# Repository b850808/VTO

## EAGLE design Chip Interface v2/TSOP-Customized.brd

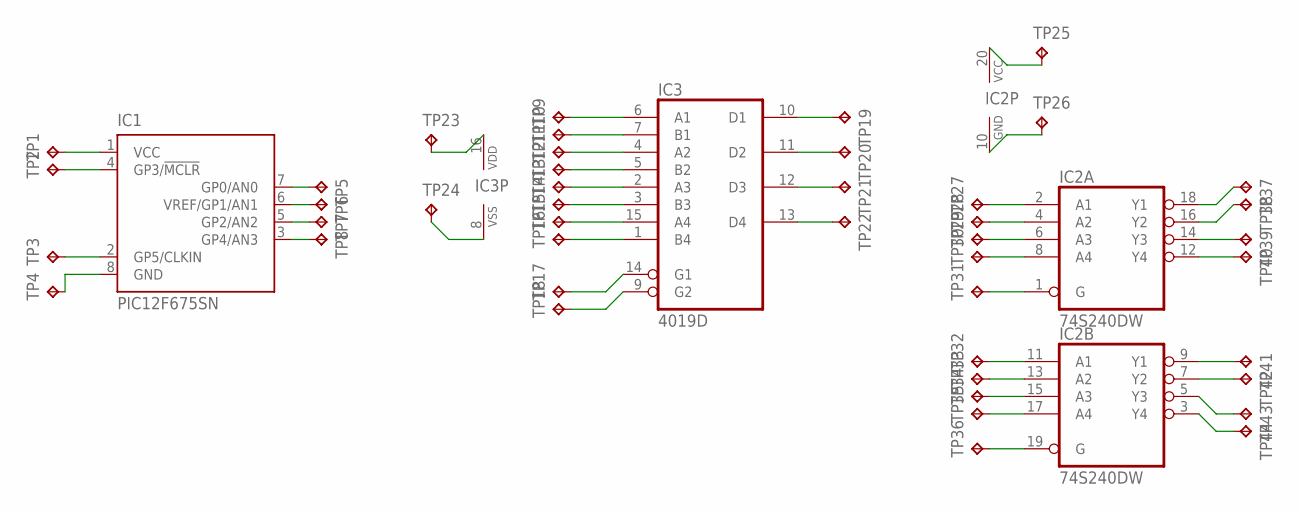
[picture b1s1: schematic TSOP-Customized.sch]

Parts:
IC1: PIC12F675SN; SO-08
IC2: 74S240DW; SO20W
IC3: 4019D; SO16
TP1, TP2, TP3, TP4, TP5, TP6, TP7, TP8, TP9, TP10, TP11, TP12, TP13, TP14, TP15, TP16, TP17, TP18, TP19, TP20, TP21, TP22, TP23, TP24, TP25, TP26, TP27, TP28, TP29, TP30, TP31, TP32, TP33, TP34, TP35, TP36, TP37, TP38, TP39, TP40, TP41, TP42, TP43, TP44: TPPAD1-13Y; P1-13Y

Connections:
unnamed: IC1.1 (VCC), TP1.TP
unnamed: IC1.4 (GP3/!MCLR), TP2.TP
unnamed: IC1.2 (GP5/CLKIN), TP3.TP
unnamed: IC1.8 (GND), TP4.TP
unnamed: IC1.3 (GP4/AN3), TP8.TP
unnamed: IC1.5 (GP2/AN2), TP7.TP
unnamed: IC1.6 (VREF/GP1/AN1), TP6.TP
unnamed: IC1.7 (GP0/AN0), TP5.TP
unnamed: IC3.6 (A1), TP9.TP
unnamed: IC3.7 (B1), TP10.TP
unnamed: IC3.4 (A2), TP11.TP
unnamed: IC3.5 (B2), TP12.TP
unnamed: IC3.2 (A3), TP13.TP
unnamed: IC3.3 (B3), TP14.TP
unnamed: IC3.15 (A4), TP15.TP
unnamed: IC3.1 (B4), TP16.TP
unnamed: IC3.14 (G1), TP17.TP
unnamed: IC3.9 (G2), TP18.TP
unnamed: IC3.13 (D4), TP22.TP
unnamed: IC3.12 (D3), TP21.TP
unnamed: IC3.11 (D2), TP20.TP
unnamed: IC3.10 (D1), TP19.TP
unnamed: IC3.8 (VSS), TP24.TP
unnamed: IC3.16 (VDD), TP23.TP
unnamed: IC2.2 (A1), TP27.TP
unnamed: IC2.4 (A2), TP28.TP
unnamed: IC2.6 (A3), TP29.TP
unnamed: IC2.8 (A4), TP30.TP
unnamed: IC2.1 (G), TP31.TP
unnamed: IC2.11 (A1), TP32.TP
unnamed: IC2.13 (A2), TP33.TP
unnamed: IC2.15 (A3), TP34.TP
unnamed: IC2.17 (A4), TP35.TP
unnamed: IC2.19 (G), TP36.TP
unnamed: IC2.20 (VCC), TP25.TP
unnamed: IC2.10 (GND), TP26.TP
unnamed: IC2.18 (Y1), TP37.TP
unnamed: IC2.16 (Y2), TP38.TP
unnamed: IC2.14 (Y3), TP39.TP
unnamed: IC2.12 (Y4), TP40.TP
unnamed: IC2.9 (Y1), TP41.TP
unnamed: IC2.7 (Y2), TP42.TP
unnamed: IC2.5 (Y3), TP43.TP
unnamed: IC2.3 (Y4), TP44.TP

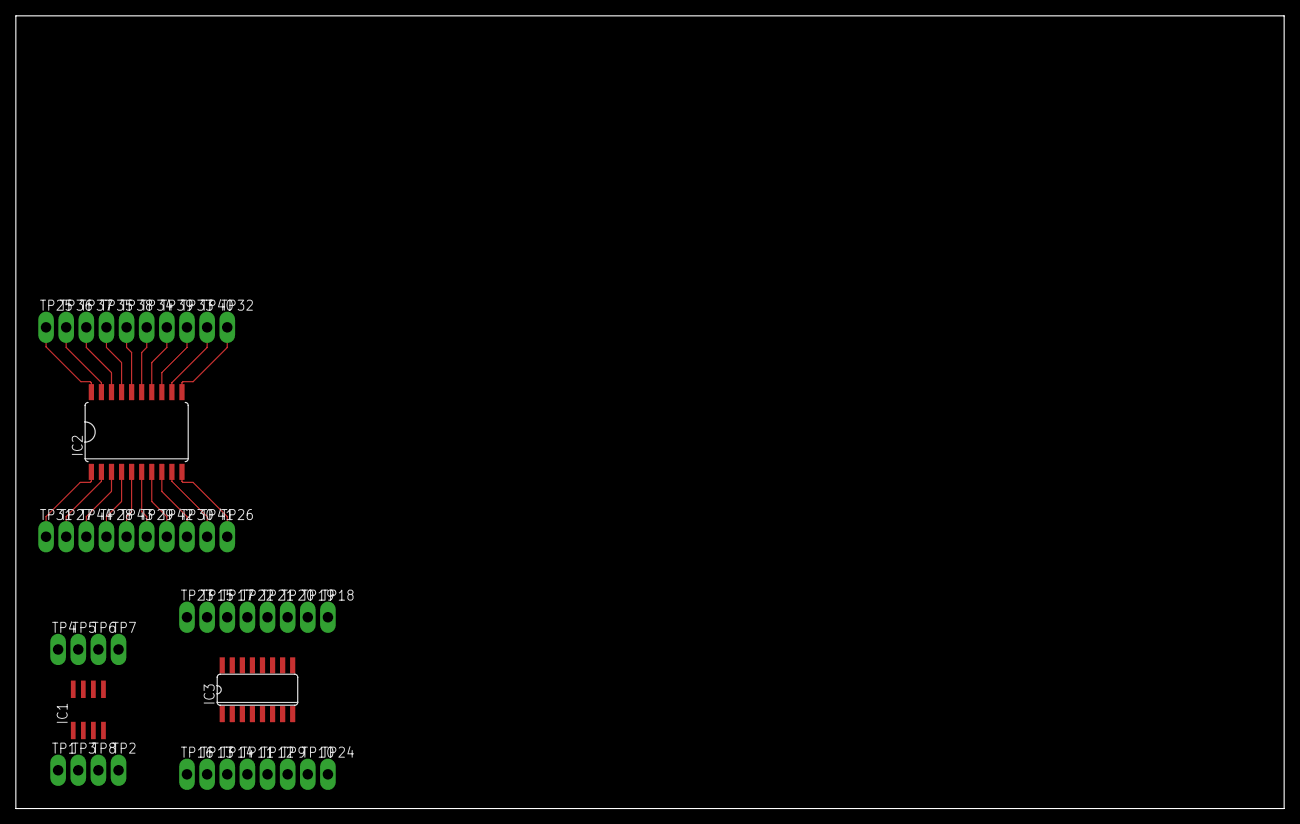
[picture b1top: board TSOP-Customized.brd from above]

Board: 2 copper layers, 160.0 x 100.0 mm, 47 parts (0 on the bottom side), 44 nets.

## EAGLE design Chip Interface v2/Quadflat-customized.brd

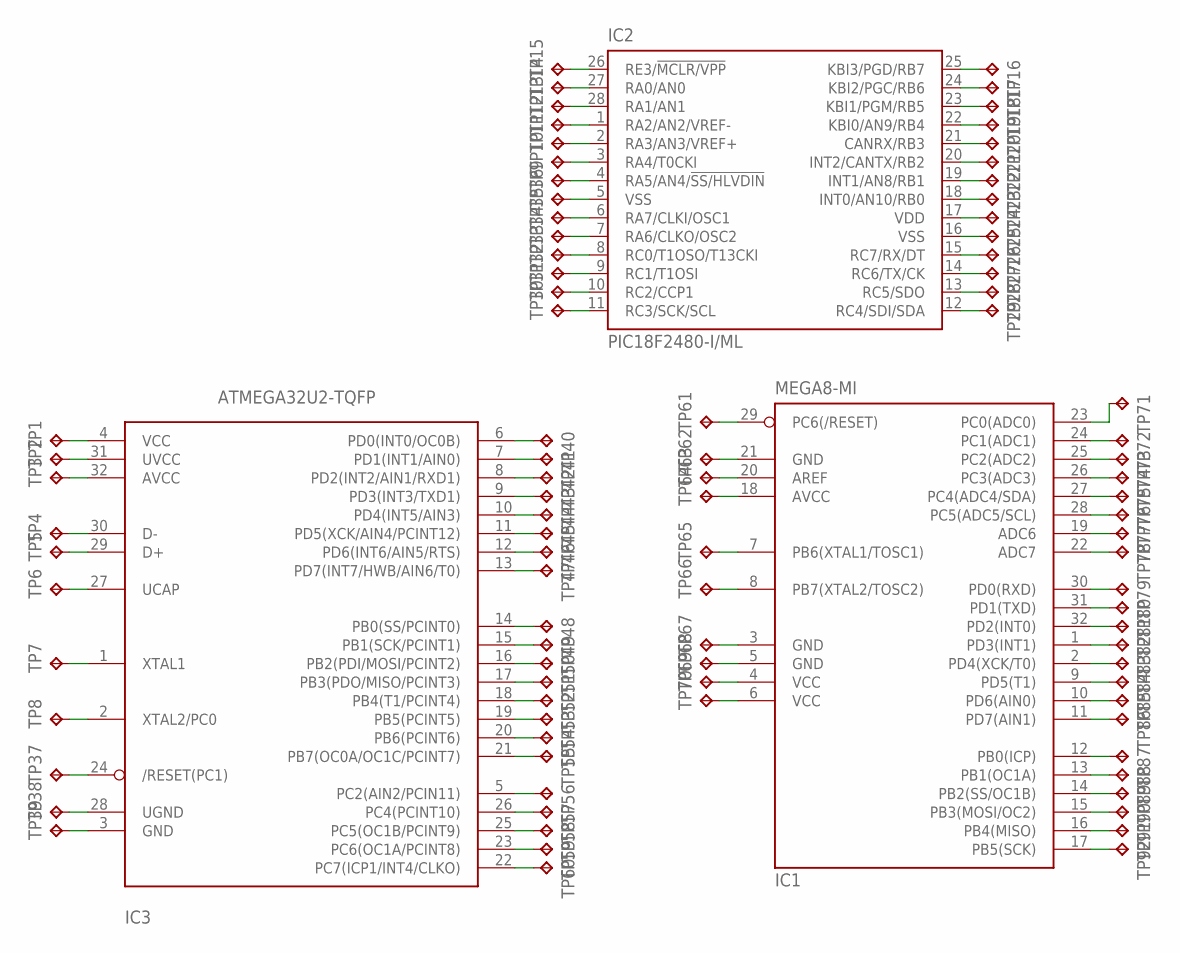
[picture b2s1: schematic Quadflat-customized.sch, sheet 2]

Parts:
IC1: MEGA8-MI; MLF32
IC2: PIC18F2480-I/ML; QFN28-ML_6X6MM
IC3: ATMEGA32U2-TQFP; TQFP32-08
TP1, TP2, TP3, TP4, TP5, TP6, TP7, TP8, TP9, TP10, TP11, TP12, TP13, TP14, TP15, TP16, TP17, TP18, TP19, TP20, TP21, TP22, TP23, TP24, TP25, TP26, TP27, TP28, TP29, TP30, TP31, TP32, TP33, TP34, TP35, TP36, TP37, TP38, TP39, TP40, TP41, TP42, TP43, TP44, TP45, TP46, TP47, TP48, TP49, TP50, TP51, TP52, TP53, TP54, TP55, TP56, TP57, TP58, TP59, TP60, TP61, TP62, TP63, TP64, TP65, TP66, TP67, TP68, TP69, TP70, TP71, TP72, TP73, TP74, TP75, TP76, TP77, TP78, TP79, TP80, TP81, TP82, TP83, TP84, TP85, TP86, TP87, TP88, TP89, TP90, TP91, TP92: TPPAD1-13Y; P1-13Y

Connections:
unnamed: IC3.4 (VCC), TP1.TP
unnamed: IC3.31 (UVCC), TP2.TP
unnamed: IC3.32 (AVCC), TP3.TP
unnamed: IC3.30 (D-), TP4.TP
unnamed: IC3.29 (D+), TP5.TP
unnamed: IC3.27 (UCAP), TP6.TP
unnamed: IC3.1 (XTAL1), TP7.TP
unnamed: IC3.2 (XTAL2/PC0), TP8.TP
unnamed: IC2.11 (RC3/SCK/SCL), TP30.TP
unnamed: IC2.10 (RC2/CCP1), TP31.TP
unnamed: IC2.9 (RC1/T1OSI), TP32.TP
unnamed: IC2.8 (RC0/T1OSO/T13CKI), TP33.TP
unnamed: IC2.7 (RA6/CLKO/OSC2), TP34.TP
unnamed: IC2.6 (RA7/CLKI/OSC1), TP35.TP
unnamed: IC2.5 (VSS), TP36.TP
unnamed: IC2.4 (RA5/AN4/!SS/HLVDIN), TP9.TP
unnamed: IC2.3 (RA4/T0CKI), TP10.TP
unnamed: IC2.2 (RA3/AN3/VREF+), TP11.TP
unnamed: IC2.1 (RA2/AN2/VREF-), TP12.TP
unnamed: IC2.28 (RA1/AN1), TP13.TP
unnamed: IC2.27 (RA0/AN0), TP14.TP
unnamed: IC2.26 (RE3/!MCLR/VPP), TP15.TP
unnamed: IC2.25 (KBI3/PGD/RB7), TP16.TP
unnamed: IC2.24 (KBI2/PGC/RB6), TP17.TP
unnamed: IC2.23 (KBI1/PGM/RB5), TP18.TP
unnamed: IC2.22 (KBI0/AN9/RB4), TP19.TP
unnamed: IC2.21 (CANRX/RB3), TP20.TP
unnamed: IC2.20 (INT2/CANTX/RB2), TP21.TP
unnamed: IC2.19 (INT1/AN8/RB1), TP22.TP
unnamed: IC2.18 (INT0/AN10/RB0), TP23.TP
unnamed: IC2.17 (VDD), TP24.TP
unnamed: IC2.16 (VSS), TP25.TP
unnamed: IC2.15 (RC7/RX/DT), TP26.TP
unnamed: IC2.14 (RC6/TX/CK), TP27.TP
unnamed: IC2.13 (RC5/SDO), TP28.TP
unnamed: IC2.12 (RC4/SDI/SDA), TP29.TP
unnamed: IC3.24 (/RESET(PC1)), TP37.TP
unnamed: IC3.28 (UGND), TP38.TP
unnamed: IC3.3 (GND), TP39.TP
unnamed: IC3.22 (PC7(ICP1/INT4/CLKO)), TP60.TP
unnamed: IC3.23 (PC6(OC1A/PCINT8)), TP59.TP
unnamed: IC3.25 (PC5(OC1B/PCINT9)), TP58.TP
unnamed: IC3.26 (PC4(PCINT10)), TP57.TP
unnamed: IC3.5 (PC2(AIN2/PCIN11)), TP56.TP
unnamed: IC3.21 (PB7(OC0A/OC1C/PCINT7)), TP55.TP
unnamed: IC3.20 (PB6(PCINT6)), TP54.TP
unnamed: IC3.19 (PB5(PCINT5)), TP53.TP
unnamed: IC3.18 (PB4(T1/PCINT4)), TP52.TP
unnamed: IC3.17 (PB3(PDO/MISO/PCINT3)), TP51.TP
unnamed: IC3.16 (PB2(PDI/MOSI/PCINT2)), TP50.TP
unnamed: IC3.15 (PB1(SCK/PCINT1)), TP49.TP
unnamed: IC3.14 (PB0(SS/PCINT0)), TP48.TP
unnamed: IC3.13 (PD7(INT7/HWB/AIN6/T0)), TP47.TP
unnamed: IC3.12 (PD6(INT6/AIN5/RTS)), TP46.TP
unnamed: IC3.11 (PD5(XCK/AIN4/PCINT12)), TP45.TP
unnamed: IC3.10 (PD4(INT5/AIN3)), TP44.TP
unnamed: IC3.9 (PD3(INT3/TXD1)), TP43.TP
unnamed: IC3.8 (PD2(INT2/AIN1/RXD1)), TP42.TP
unnamed: IC3.7 (PD1(INT1/AIN0)), TP41.TP
unnamed: IC3.6 (PD0(INT0/OC0B)), TP40.TP
unnamed: IC1.29 (PC6(/RESET)), TP61.TP
unnamed: IC1.21 (GND), TP62.TP
unnamed: IC1.20 (AREF), TP63.TP
unnamed: IC1.18 (AVCC), TP64.TP
unnamed: IC1.7 (PB6(XTAL1/TOSC1)), TP65.TP
unnamed: IC1.8 (PB7(XTAL2/TOSC2)), TP66.TP
unnamed: IC1.3 (GND), TP67.TP
unnamed: IC1.5 (GND), TP68.TP
unnamed: IC1.4 (VCC), TP69.TP
unnamed: IC1.6 (VCC), TP70.TP
unnamed: IC1.23 (PC0(ADC0)), TP71.TP
unnamed: IC1.24 (PC1(ADC1)), TP72.TP
unnamed: IC1.25 (PC2(ADC2)), TP73.TP
unnamed: IC1.26 (PC3(ADC3)), TP74.TP
unnamed: IC1.27 (PC4(ADC4/SDA)), TP75.TP
unnamed: IC1.28 (PC5(ADC5/SCL)), TP76.TP
unnamed: IC1.19 (ADC6), TP77.TP
unnamed: IC1.22 (ADC7), TP78.TP
unnamed: IC1.30 (PD0(RXD)), TP79.TP
unnamed: IC1.31 (PD1(TXD)), TP80.TP
unnamed: IC1.32 (PD2(INT0)), TP81.TP
unnamed: IC1.1 (PD3(INT1)), TP82.TP
unnamed: IC1.2 (PD4(XCK/T0)), TP83.TP
unnamed: IC1.9 (PD5(T1)), TP84.TP
unnamed: IC1.10 (PD6(AIN0)), TP85.TP
unnamed: IC1.11 (PD7(AIN1)), TP86.TP
unnamed: IC1.12 (PB0(ICP)), TP87.TP
unnamed: IC1.13 (PB1(OC1A)), TP88.TP
unnamed: IC1.14 (PB2(SS/OC1B)), TP89.TP
unnamed: IC1.15 (PB3(MOSI/OC2)), TP90.TP
unnamed: IC1.16 (PB4(MISO)), TP91.TP
unnamed: IC1.17 (PB5(SCK)), TP92.TP

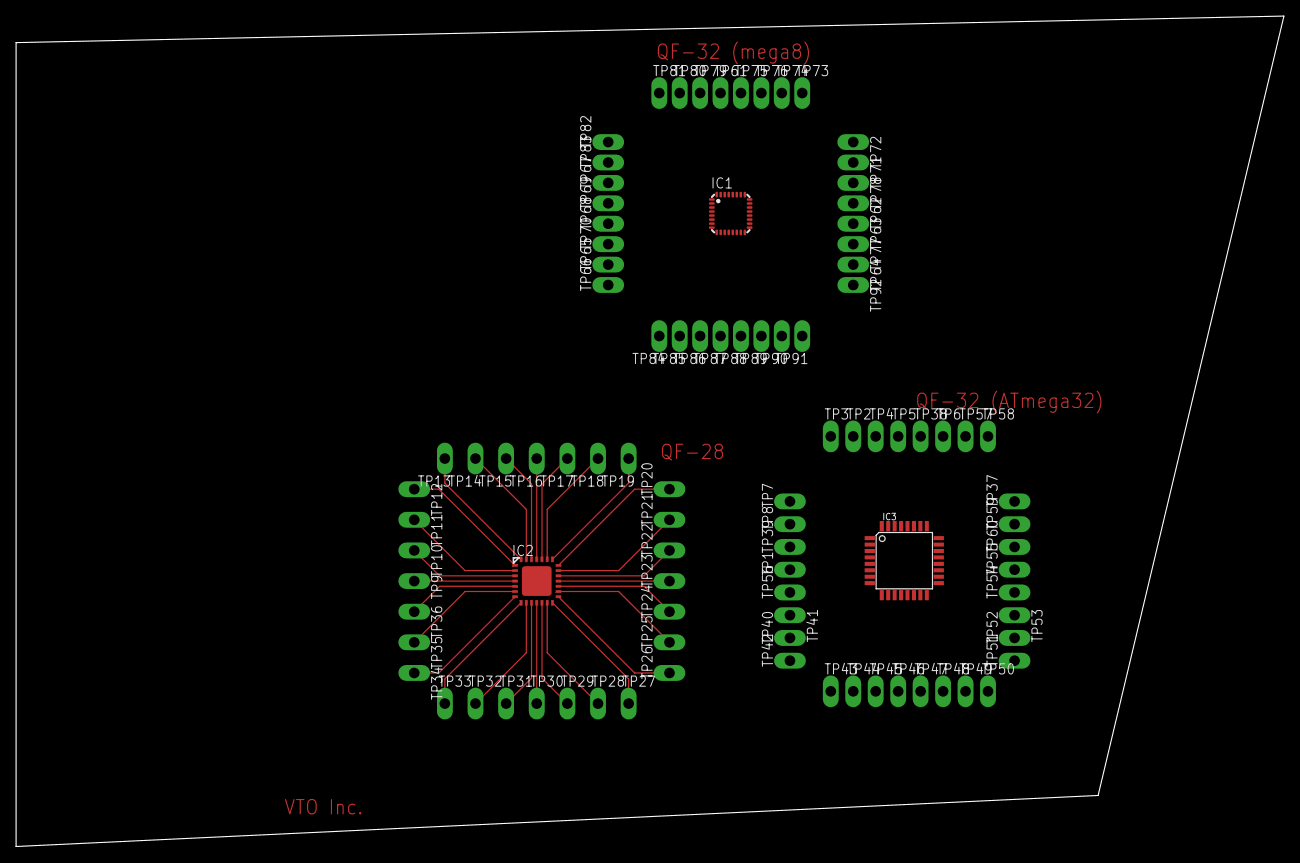
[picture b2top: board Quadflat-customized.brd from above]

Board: 2 copper layers, 157.7 x 103.3 mm, 95 parts (0 on the bottom side), 92 nets.

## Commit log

2018-06-07 Uploaded current eagle files
